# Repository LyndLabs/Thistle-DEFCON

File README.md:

## Thistle Badge
`coming soon`

## Thistle SAO

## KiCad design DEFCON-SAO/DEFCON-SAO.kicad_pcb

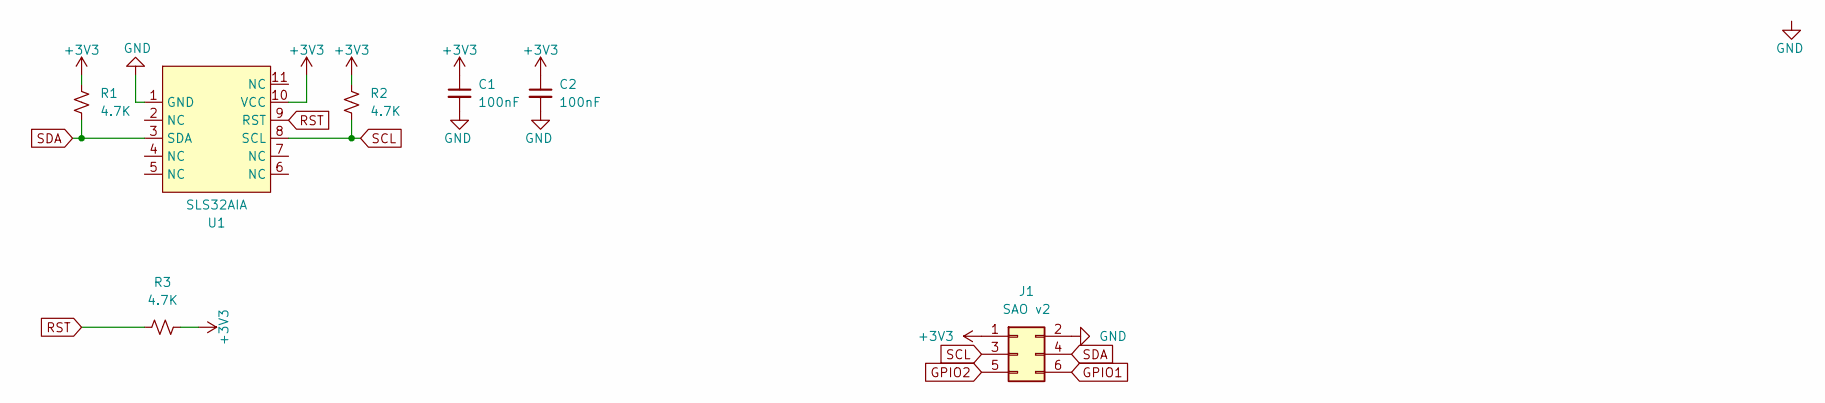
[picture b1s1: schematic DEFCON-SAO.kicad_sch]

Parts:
C1, C2: 100nF; C_0603_1608Metric
J1: SAO v2; PinSocket_2x03_P2.54mm_Vertical_SMD
R1, R2, R3: 4.7K; R_0603_1608Metric
U1: SLS32AIA; USON-10-1EP_3x3mm_P0.5mm_EP1.5x2.3mm

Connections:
+3V3: C1.1, C2.1, J1.1, R1.1, R2.1, R3.2, U1.10 (VCC)
GND: C1.2, C2.2, J1.2, U1.1 (GND), U1.11 (NC)
GPIO1: J1.6
GPIO2: J1.5
RST: R3.1, U1.9 (RST)
SCL: J1.3, R2.2, U1.8 (SCL)
SDA: J1.4, R1.2, U1.3 (SDA)

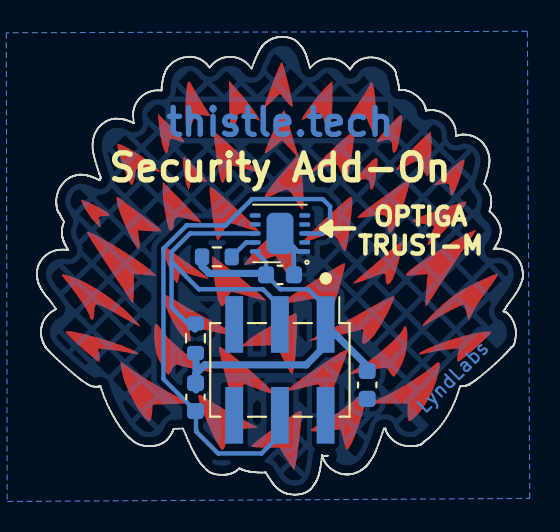
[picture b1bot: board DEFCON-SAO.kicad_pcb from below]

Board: 2 copper layers, 27.0 x 25.4 mm, 7 parts (7 on the bottom side), 5 nets.

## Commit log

2025-06-03 push v0 SAO
